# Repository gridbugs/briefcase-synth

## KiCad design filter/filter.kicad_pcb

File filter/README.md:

# Filter

## 2024-08-23

- There's a failure mode where the output is silent and one of the
  resonance LEDs is solid on and the other is solid off. This seems to
  mean that the TL074 is damaged. It seems that this circuit damages
  the TL074 when certain pins are connected by accident. There's also
  a failure mode that damages the LM13700. Not sure what causes that.
- Next time don't bother including the high-pass filter. It
  complicates the circuit and UI, is not likely to be used, and
  doesn't work particularly well. Build a dedicated high-pass filter
  if necessary.
- The circuit has a bug where the volume of the self-oscillation
  signal drops quickly above a certain frequency. This has the effect
  of limiting the effect of resonance. This is only a bug in the final
  implementation of the filter; breadboard implementations of the
  design don't have this problem.
- The stripboard is slightly too large to comfortably fit in the case.
- Using a safety pin to group cables together and drilling a hole in
  the stripboard for cable management was effective at reducing the
  tangle of cables and made it easy to work on the circuit after
  starting work on the front panel.
- Build a subset of the circuit first. Use self-oscillation to test
  the circuit incrementally as it's built.
  
## 2024-08-25

- Rebuilt about half the circuit, intermittently testing against a
  breadboard implementation.
- One issue that came up was the cutoff potentiometer not responding
  sometimes. Reflowing its connection to the board seemed to fix the
  problem.

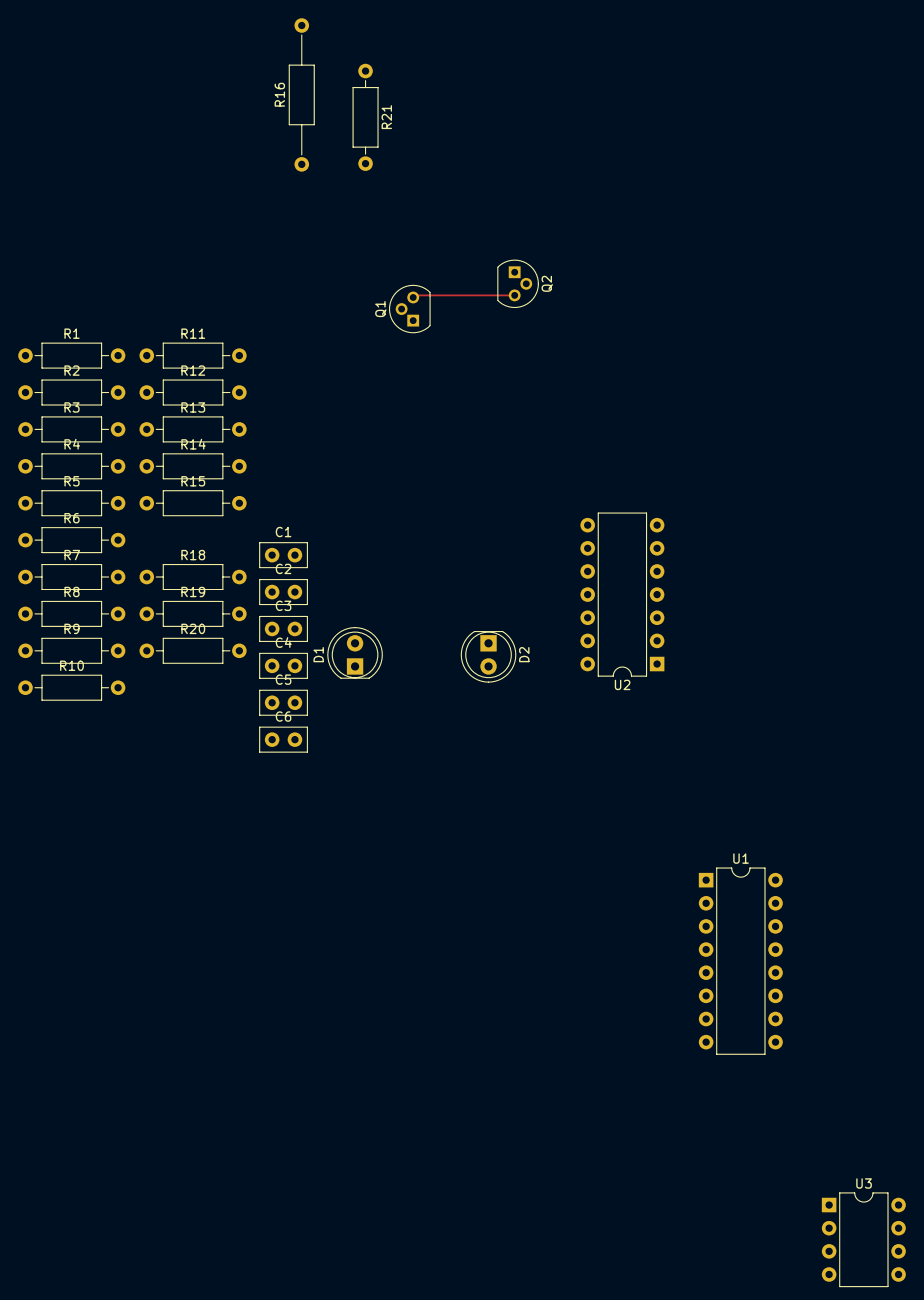
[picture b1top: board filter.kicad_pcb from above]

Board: 2 copper layers, 33 parts (0 on the bottom side), 24 nets.

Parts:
C1, C2: 100nf; C_Disc_D5.0mm_W2.5mm_P2.50mm
C3, C6: 1nf; C_Disc_D5.0mm_W2.5mm_P2.50mm
C4: 470nf; C_Disc_D5.0mm_W2.5mm_P2.50mm
C5: 4.7nf; C_Disc_D5.0mm_W2.5mm_P2.50mm
D1, D2: LED; LED_D5.0mm
Q1, Q2: PNP; TO-92
R1, R2, R6, R7, R8, R10, R12: 10k; R_Axial_DIN0207_L6.3mm_D2.5mm_P10.16mm_Horizontal
R3, R5, R9, R11: 220R; R_Axial_DIN0207_L6.3mm_D2.5mm_P10.16mm_Horizontal
R4, R15: 1k8; R_Axial_DIN0207_L6.3mm_D2.5mm_P10.16mm_Horizontal
R13: 4k7; R_Axial_DIN0207_L6.3mm_D2.5mm_P10.16mm_Horizontal
R14: 470k; R_Axial_DIN0207_L6.3mm_D2.5mm_P10.16mm_Horizontal
R16: 100k; R_Axial_DIN0207_L6.3mm_D2.5mm_P15.24mm_Horizontal
R18, R19, R20, R21: 100k; R_Axial_DIN0207_L6.3mm_D2.5mm_P10.16mm_Horizontal
U1: LM13700; DIP-16_W7.62mm
U2: TL074; DIP-14_W7.62mm
U3: TL072; DIP-8_W7.62mm

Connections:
+12V: C2.2, U1.11 (V+), U2.4 (V+), U3.8 (V+)
-12V: C1.1, R14.2, U1.6 (V-), U2.11 (V-), U3.4 (V-)
GND: C1.2, C2.1, C6.1, Q2.2 (B), R3.2, R4.2, R5.1, R9.2, R11.2, R15.1, U2.12 (+), U3.3 (+)
Input: R2.2, R20.2
unnamed: C4.2, R19.1
unnamed: C5.1, R13.2, U2.14
unnamed: C3.1, D1.2 (A), D2.1 (K), R6.1, U2.1
unnamed: D1.1 (K), D2.2 (A), R4.1, R6.2, U2.2 (-)
unnamed: Q1.2 (B), R15.2, R16.1, R21.2
unnamed: C5.2, Q1.1 (C), R14.1, U2.13 (-)
unnamed: Q1.3 (E), Q2.3 (E), R13.1
unnamed: Q2.1 (C), R7.1, R12.1
unnamed: R7.2, U1.1
unnamed: R12.2, U1.16
unnamed: R18.2, U3.1
unnamed: R8.2, R9.1, U1.14 (+)
unnamed: R10.1, R11.1, U1.13 (-)
unnamed: R5.2, U1.3 (+)
unnamed: R1.2, R2.1, R3.1, U1.4 (-)
unnamed: C3.2, U1.5, U2.5 (+)
unnamed: R1.1, R8.1, U2.6 (-), U2.7
unnamed: C6.2, U1.12, U2.10 (+)
unnamed: C4.1, R10.2, U2.8, U2.9 (-)
unnamed: R18.1, R19.2, R20.1, U3.2 (-)

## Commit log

2024-07-16 Remove geometry, add power supply schematic
2024-07-16 Add oscillator
2024-07-17 Add noise circuit to oscillator
2024-07-28 Update oscillator schematic after building it
2024-07-30 Update oscillator
2024-07-31 Note about PWM
2024-08-01 Improve oscillator bass
2024-08-01 Add mixer circuit
2024-08-07 Start low-pass filter
2024-08-14 Tidy up low-pass filter schematic
2024-08-15 Update low pass filter
2024-08-15 Update lpf pdf
2024-08-18 Maybe fix bug in low-pass filter
2024-08-18 Revert "Maybe fix bug in low-pass filter"
    It was right the first time.
    This reverts commit b62497d0d33f661917a797e78c2c214d61ac51a2.
2024-08-21 Add simple self oscillator test circuit
2024-08-21 Rename self oscillator
2024-08-21 Rename low-pass-filter to filter
2024-08-21 Experiment with pcb
2024-08-22 Add some notes
2024-08-23 Update notes
2024-08-24 Notes
2024-08-28 Fix typo in oscillator
2024-08-28 Remove high-pass filter switch from filter
2024-08-28 Rename filter to low-pass-filter
2024-08-31 Update oscillator notes
2024-09-01 Fix some tyos in oscillator
2024-09-01 Add simple 3340 test circuit
2024-09-06 Change oscillator resistor to match AS3340 notes
2024-09-11 Add attenuverter circuit
2024-09-23 Dual mixer
2024-09-23 Add disconnection
2024-09-26 Fixes for dual mixer
2024-10-01 Update dual mixer
2024-10-06 Bootstrap clock arduino project
2024-10-06 Envelope generator schematic
2024-10-06 Add some envelope generator notes
2024-10-06 Add missing clock files
2024-10-06 Corrections to envelope generator
2024-10-06 Add clock schematic
2024-10-06 Add note to envelope generator
2024-11-10 Reverb driver schematic
2024-11-11 Simple DAC example in quantizer arduino project
2024-11-13 Write code for quantizer
2024-11-16 Fix error in envolpe generator schematic
2024-11-18 Mostly implement clock
2024-11-18 Fix clock bug
2024-11-18 Fix issue causing inconsistent timing
2024-11-18 Update clock schematic
2024-12-08 Finish code for quantizer
2024-12-16 Add sample and hold schematic
2024-12-16 Add quantizer schematic
2024-12-16 Quantizer update
2024-12-29 Add a resistor to sample-and-hold
2024-12-30 Oscillator note
2024-12-30 Fix typo
2025-01-25 Add low frequency mixer
2025-01-25 Add note to reverb circuit
2025-05-25 Add midi to cv module
2025-05-25 Add test scales to quantizer
